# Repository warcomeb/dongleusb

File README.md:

# dongleusb
Dongle USB to the rest of World by UART communication

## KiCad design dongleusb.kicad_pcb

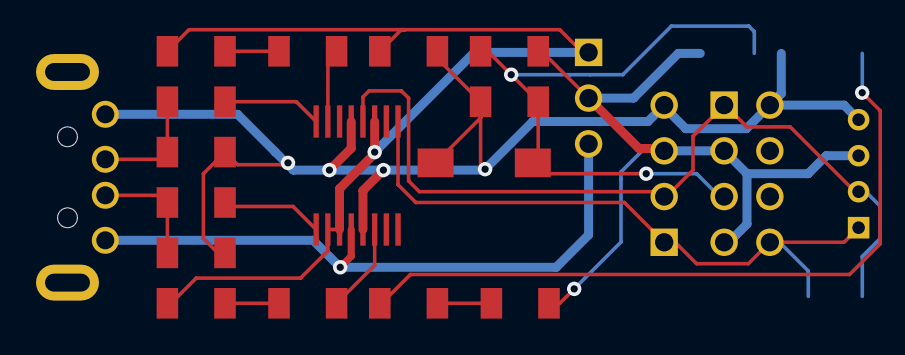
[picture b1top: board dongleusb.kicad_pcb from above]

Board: 2 copper layers, 22 parts (0 on the bottom side), 17 nets.

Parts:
C1, C2: 47p; W-PASSIVE-1206
C3, C4: 100n; W-PASSIVE-1206
D1, D2, D3: LED; W-LED-1206
JP1: ENABLE_VCC; W-CONN-3x1-STRIP
P1: USB; W-CONN-USB-A-MULTICOMP-THT
P5: ESP8266; W-CONN-4x2-STRIP
P6: UART_TERMINAL; W-CONN-4x1-STRIP
P7: UART_GROVE; W-CONN-4x1-JST
R1, R2: 27; W-PASSIVE-1206
R3, R4, R5, R6: 270; W-PASSIVE-1206
SW1: RESET; W-SWITCH-EVQPE1
U1: FT230XS; W-IC-TSSOP-16
U2: HM-11; W-IC-HM11
VAL: REF; W-LOGO-4MM

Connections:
+3.3V: C3.1, D2.1, D3.1, JP1.1, U1.3, U1.10, U1.11
+5V: JP1.3, P1.1, U1.12
/LED_COMM: R3.2, U2.15
/RESET: C4.1, P5.5, R6.2, SW1.1, U2.11
/UART_RX: P5.8, P6.1, P7.1, U1.1, U2.4
/UART_TX: P5.1, P6.2, P7.2, U1.4, U2.2
/VCC: D1.1, JP1.2, P5.3, P5.7, P6.3, P7.3, R6.1, U2.9
GND: C1.2, C2.2, C3.2, C4.2, P1.4, P5.2, P6.4, P7.4, SW1.2, U1.5, U1.13, U2.12
unnamed: D1.2, R3.1
unnamed: R5.2, U1.7
unnamed: R4.2, U1.14
unnamed: D2.2, R4.1
unnamed: D3.2, R5.1
unnamed: C2.1, P1.3, R2.1
unnamed: R1.2, U1.9
unnamed: R2.2, U1.8
unnamed: C1.1, P1.2, R1.1

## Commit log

2015-03-12 Created Kicad project and added license file.
2015-03-12 Added license type and started to design the board's schematic
2015-03-16 Added BOM informations in USB connector and grove connector.
2015-03-18 Added all communication interfaces. Added LED and reset connection. Started to design PCB.
2015-03-19 Added LEDs informations. Added USB footprint. Placed some components into layout.
2015-03-23 Placed all components. Added some commercial informations of communications modules.
2015-03-24 Connected all nets into layout.
2015-07-09 Added my logo
2015-07-09 Added gerber files of revision 0
2015-07-09 Added open hardware logo's library.
2015-07-09 Added documents folder for datasheets and other
2015-07-09 Added some files for production, the bill of materials is not still ready!
2015-08-10 Ended bill of materials.
2015-08-10 Added bill of materials formatted in a production folder.
